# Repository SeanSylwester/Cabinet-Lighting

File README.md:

# Cabinet-Lighting
Automatic cabinet lighting using a reed switch

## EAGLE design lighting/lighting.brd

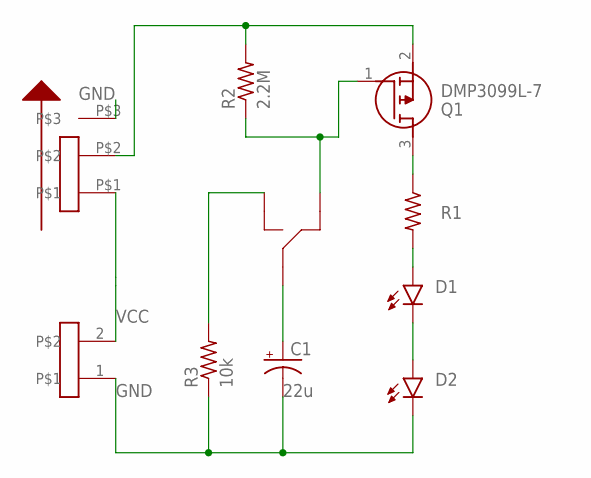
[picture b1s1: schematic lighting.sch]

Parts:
C1: WE-CAP
D1, D2: LUXEON2835C
J1: 22-05-3021; 7395-02
Q1: DMP3099L-7; SOT96P240X120-3N
R1: R-US_R1210; R1210
R2: 2.2M; R1206
R3: 10k; R1206
S2: CL-SB-12B-01T
U$1: KSK-1C90U

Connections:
COM: C1.+, U$1.COM
GND: C1.-, D2.- (C), J1.1, R3.1, S2.P$3
unnamed: D1.- (C), D2.+ (A)
unnamed: D1.+ (A), R1.2
unnamed: Q1.3 (D), R1.1
NC: Q1.1 (G), R2.1, U$1.NC
NO: R3.2, U$1.NO
PWR: Q1.2 (S), R2.2, S2.P$2
VCC: J1.2, S2.P$1

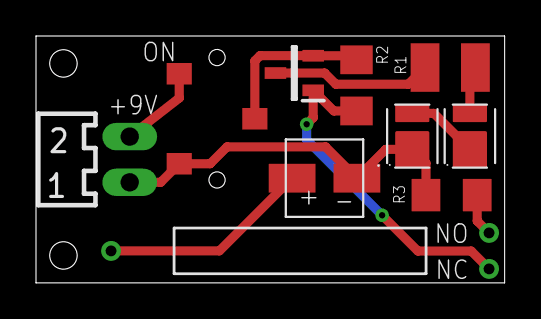
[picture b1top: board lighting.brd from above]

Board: 2 copper layers, 26.0 x 13.7 mm, 10 parts (0 on the bottom side), 9 nets.

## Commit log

2019-06-08 fixed LED direction; GND plane
2019-06-08 added BOM
2019-06-12 added mounting holes
2019-06-20 added sim; added switch-off timer; updated pcb
